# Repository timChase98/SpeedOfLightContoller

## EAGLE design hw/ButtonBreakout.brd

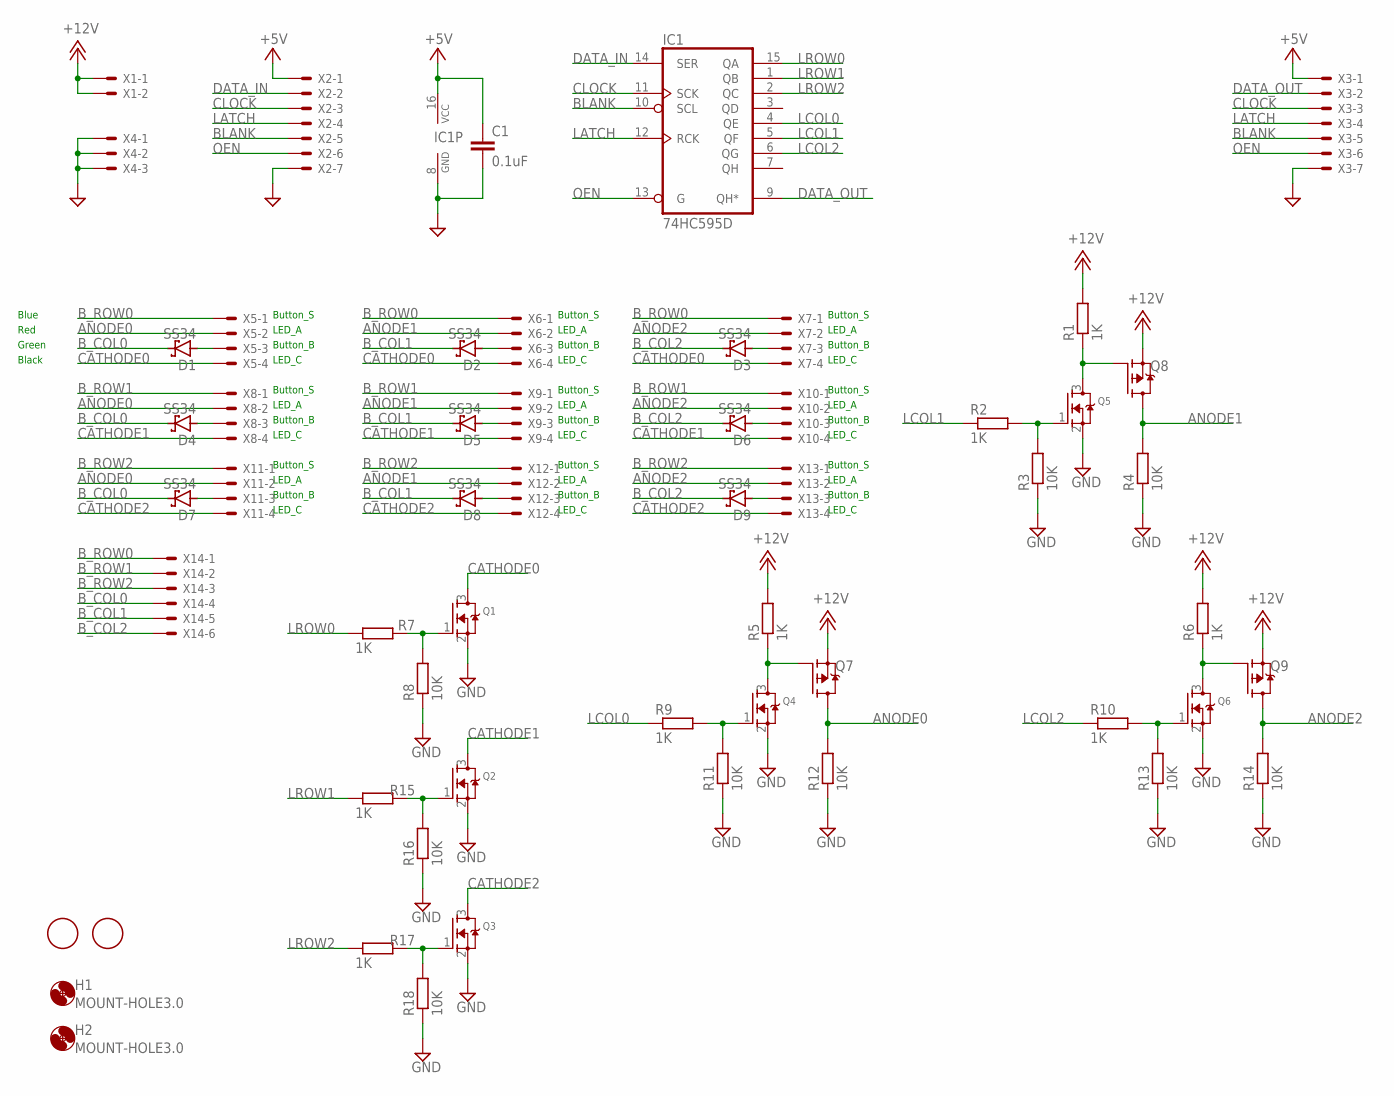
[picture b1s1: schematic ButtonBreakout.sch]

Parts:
C1: 0.1uF; C0805
D1, D2, D3, D4, D5, D6, D7, D8, D9: SS34; SMA
F1, F2: FIDUCIAL; FIDUCIAL_1MM
H1, H2: MOUNT-HOLE3.0; 3,0
IC1: 74HC595D; SO16
Q1, Q2, Q3, Q4, Q5, Q6: AO3414SOT23; SOT95P240X110-3N
Q7, Q8, Q9: AO3415; SOT95P240X110-3N
R1, R2, R5, R6, R7, R9, R10, R15, R17: 1K; R0805
R3, R4, R8, R11, R12, R13, R14, R16, R18: 10K; R0805
X1: JST-XH-02-PIN-LONG-PAD; JST-XH-02-PACKAGE-LONG-PAD
X2, X3: JST-XH-07-PIN-LONG-PAD; JST-XH-07-PACKAGE-LONG-PAD
X4: JST-XH-03-PIN-LONG-PAD; JST-XH-03-PACKAGE-LONG-PAD
X5, X6, X7, X8, X9, X10, X11, X12, X13: JST-XH-04-PIN-LONG-PAD; JST-XH-04-PACKAGE-LONG-PAD
X14: JST-XH-06-PIN-LONG-PAD; JST-XH-06-PACKAGE-LONG-PAD

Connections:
+5V: C1.1, IC1.16 (VCC), X2.1, X3.1
+12V: Q7.2 (S), Q8.2 (S), Q9.2 (S), R1.2, R5.2, R6.2, X1.1, X1.2
ANODE0: Q7.3 (D), R12.2, X5.2, X8.2, X11.2
ANODE1: Q8.3 (D), R4.2, X6.2, X9.2, X12.2
ANODE2: Q9.3 (D), R14.2, X7.2, X10.2, X13.2
BLANK: IC1.10 (SCL), X2.5, X3.5
B_COL0: D1.C, D4.C, D7.C, X14.4
B_COL1: D2.C, D5.C, D8.C, X14.5
B_COL2: D3.C, D6.C, D9.C, X14.6
B_ROW0: X5.1, X6.1, X7.1, X14.1
B_ROW1: X8.1, X9.1, X10.1, X14.2
B_ROW2: X11.1, X12.1, X13.1, X14.3
CATHODE0: Q1.3 (D), X5.4, X6.4, X7.4
CATHODE1: Q2.3 (D), X8.4, X9.4, X10.4
CATHODE2: Q3.3 (D), X11.4, X12.4, X13.4
CLOCK: IC1.11 (SCK), X2.3, X3.3
DATA_IN: IC1.14 (SER), X2.2
DATA_OUT: IC1.9 (QH*), X3.2
GND: C1.2, IC1.8 (GND), Q1.2 (S), Q2.2 (S), Q3.2 (S), Q4.2 (S), Q5.2 (S), Q6.2 (S), R3.1, R4.1, R8.1, R11.1, R12.1, R13.1, R14.1, R16.1, R18.1, X2.7, X3.7, X4.1, X4.2, X4.3
LATCH: IC1.12 (RCK), X2.4, X3.4
LCOL0: IC1.4 (QE), R9.1
LCOL1: IC1.5 (QF), R2.1
LCOL2: IC1.6 (QG), R10.1
LROW0: IC1.15 (QA), R7.1
LROW1: IC1.1 (QB), R15.1
LROW2: IC1.2 (QC), R17.1
unnamed: Q2.1 (G), R15.2, R16.2
unnamed: Q3.1 (G), R17.2, R18.2
unnamed: Q5.3 (D), Q8.1 (G), R1.1
unnamed: Q5.1 (G), R2.2, R3.2
unnamed: Q1.1 (G), R7.2, R8.2
unnamed: Q4.3 (D), Q7.1 (G), R5.1
unnamed: D1.A, X5.3
unnamed: D2.A, X6.3
unnamed: D3.A, X7.3
unnamed: D4.A, X8.3
unnamed: D5.A, X9.3
unnamed: D6.A, X10.3
unnamed: D7.A, X11.3
unnamed: D8.A, X12.3
unnamed: D9.A, X13.3
unnamed: Q4.1 (G), R9.2, R11.2
unnamed: Q6.3 (D), Q9.1 (G), R6.1
unnamed: Q6.1 (G), R10.2, R13.2
OEN: IC1.13 (G), X2.6, X3.6

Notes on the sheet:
LED_A
LED_C
Button_S
Button_B
Red
Black
Blue
Green

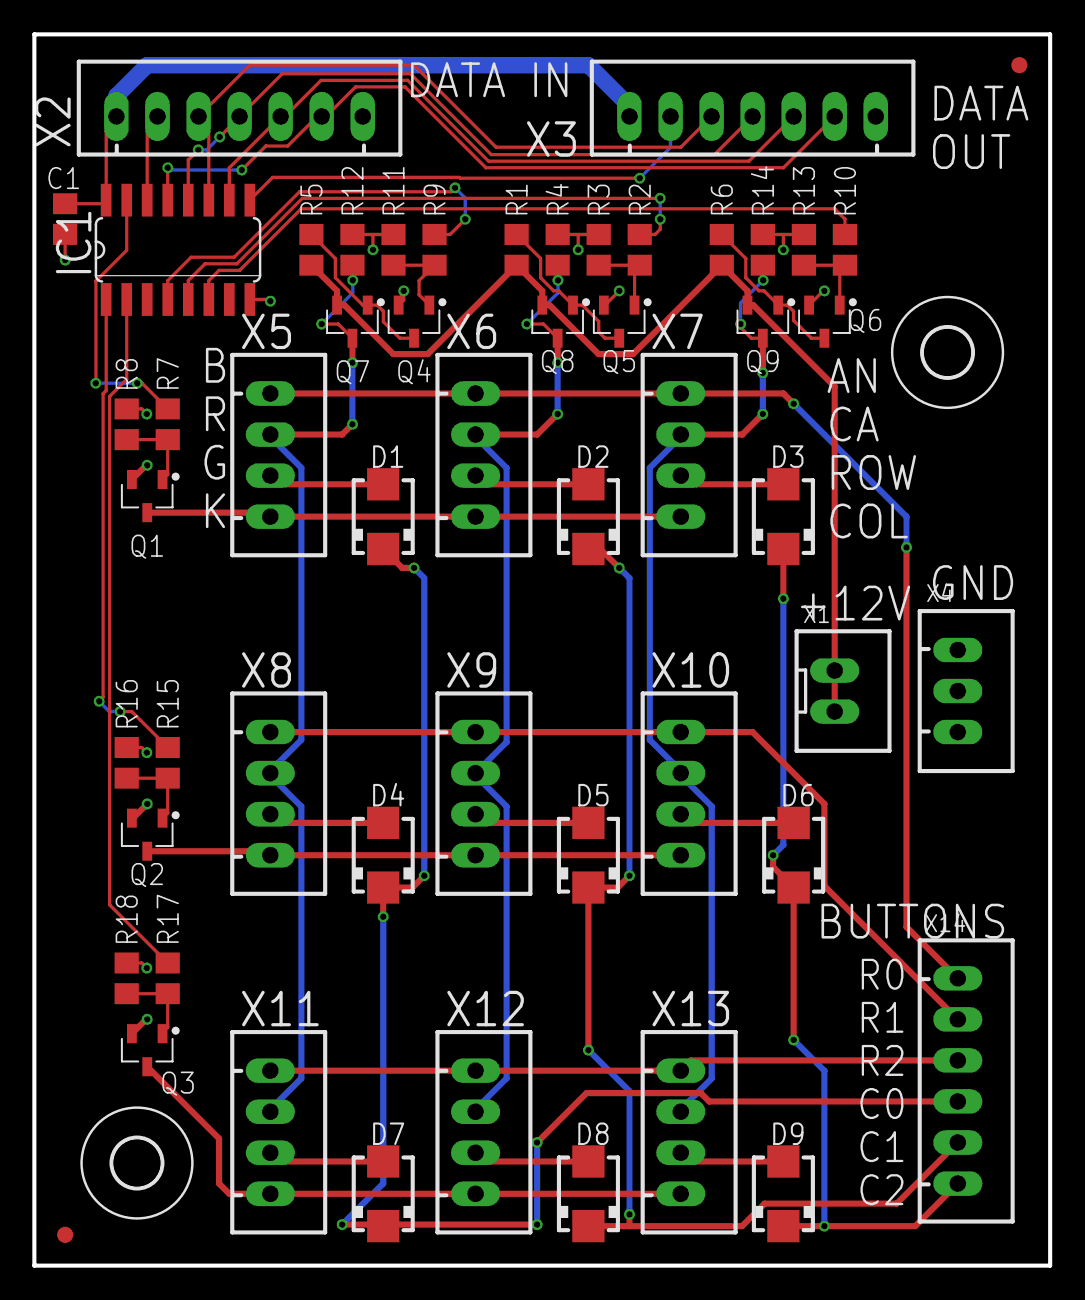
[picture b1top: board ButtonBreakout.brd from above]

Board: 2 copper layers, 62.9 x 76.2 mm, 56 parts (0 on the bottom side), 45 nets.

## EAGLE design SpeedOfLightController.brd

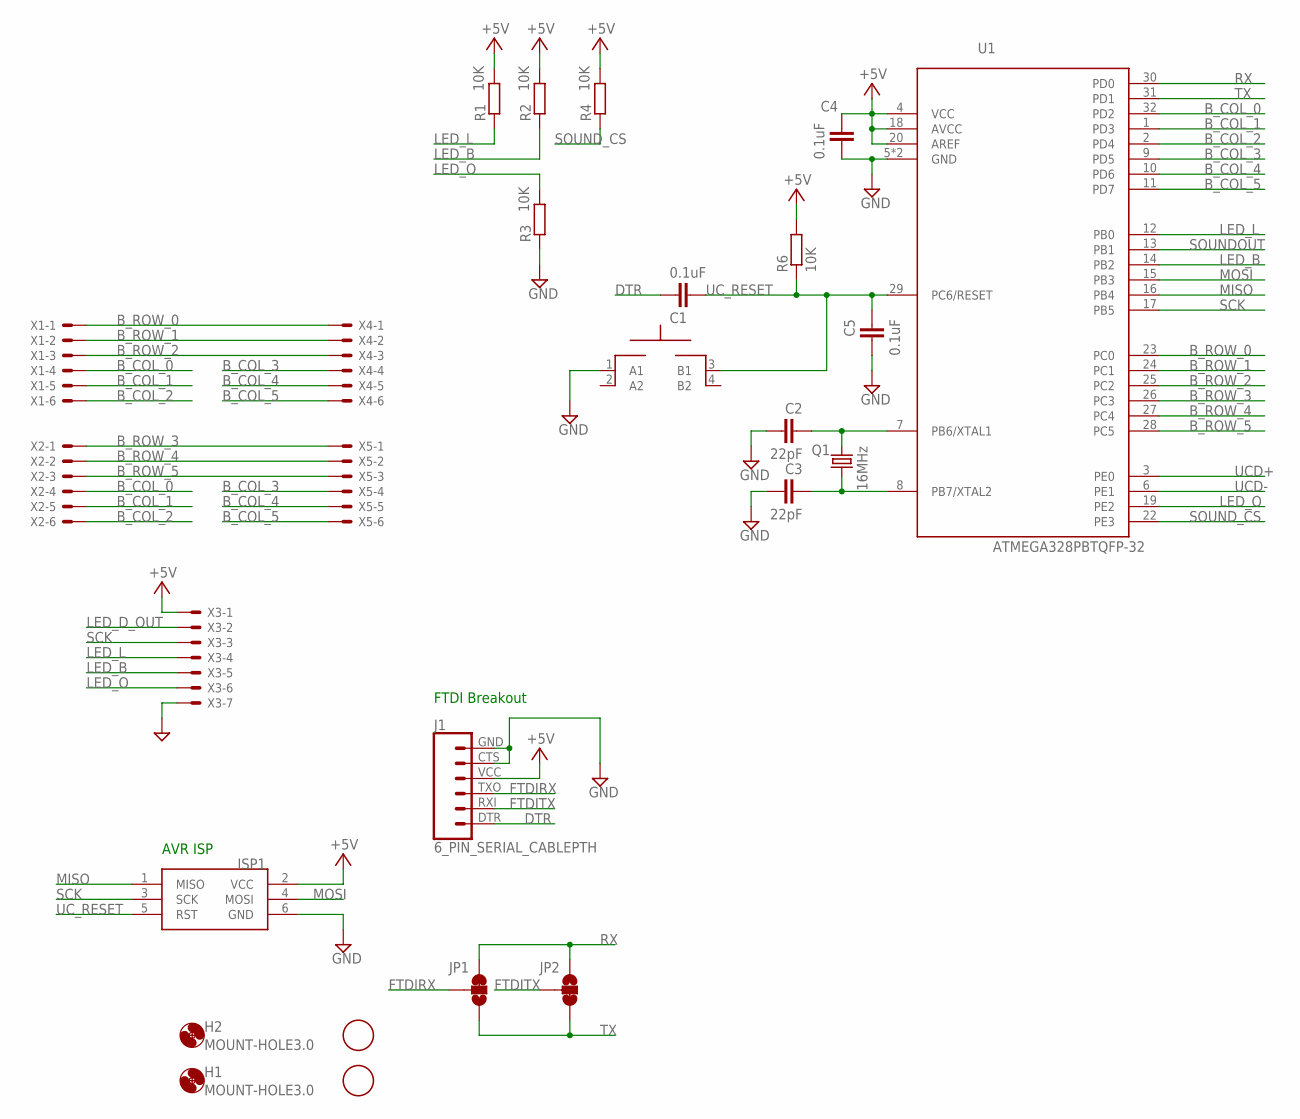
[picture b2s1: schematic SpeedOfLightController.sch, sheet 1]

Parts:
C1, C4, C5: 0.1uF; C0805
C2, C3: 22pF; C0805
F1, F2: FIDUCIAL; FIDUCIAL_1MM
H1, H2: MOUNT-HOLE3.0; 3,0
ISP1: AVRISP-6; AVRISP
J1: 6_PIN_SERIAL_CABLEPTH; FTDI_BASIC
JP1, JP2: JUMPER-SMT_3_1-NC_TRACE_SILK; SMT-JUMPER_3_1-NC_TRACE_SILK
Q1: 16MHz; HC49UP
R1, R2, R3, R4, R6: 10K; R0805
SW1: MOMENTARYBUTTON; SPST_NO_SMD
U1: ATMEGA328PBTQFP-32; QFP80P900X900X120-32N
X1, X2, X4, X5: JST-XH-06-PIN-LONG-PAD; JST-XH-06-PACKAGE-LONG-PAD
X3: JST-XH-07-PIN-LONG-PAD; JST-XH-07-PACKAGE-LONG-PAD

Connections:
+5V: C4.2, ISP1.2 (VCC), J1.VCC (4), R1.2, R2.2, R4.2, R6.2, U1.4 (VCC), U1.18 (AVCC), U1.20 (AREF), X3.1; also elsewhere on the board
B_COL_0: U1.32 (PD2), X1.4, X2.4
B_COL_1: U1.1 (PD3), X1.5, X2.5
B_COL_2: U1.2 (PD4), X1.6, X2.6
B_COL_3: U1.9 (PD5), X4.4, X5.4
B_COL_4: U1.10 (PD6), X4.5, X5.5
B_COL_5: U1.11 (PD7), X4.6, X5.6
B_ROW_0: U1.23 (PC0), X1.1, X4.1
B_ROW_1: U1.24 (PC1), X1.2, X4.2
B_ROW_2: U1.25 (PC2), X1.3, X4.3
B_ROW_3: U1.26 (PC3), X2.1, X5.1
B_ROW_4: U1.27 (PC4), X2.2, X5.2
B_ROW_5: U1.28 (PC5), X2.3, X5.3
DTR: C1.2, J1.DTR (1)
FTDIRX: J1.TXO (3), JP1.2
FTDITX: J1.RXI (2), JP2.2
GND: C2.1, C3.1, C4.1, C5.1, ISP1.6 (GND), J1.CTS (5), J1.GND (6), R3.1, SW1.1 (A1), U1.5 (GND), U1.21 (GND), X3.7; also elsewhere on the board
LED_B: R2.1, U1.14 (PB2), X3.5; also elsewhere on the board
LED_D_OUT: X3.2; also elsewhere on the board
LED_L: R1.1, U1.12 (PB0), X3.4; also elsewhere on the board
LED_O: R3.2, U1.19 (PE2), X3.6; also elsewhere on the board
MISO: ISP1.1 (MISO), U1.16 (PB4); also elsewhere on the board
MOSI: ISP1.4 (MOSI), U1.15 (PB3); also elsewhere on the board
unnamed: C2.2, Q1.1, U1.7 (PB6/XTAL1)
unnamed: C3.2, Q1.2, U1.8 (PB7/XTAL2)
RX: JP1.3, JP2.1, U1.30 (PD0)
SCK: ISP1.3 (SCK), U1.17 (PB5), X3.3; also elsewhere on the board
SOUNDOUT: U1.13 (PB1); also elsewhere on the board
SOUND_CS: R4.1, U1.22 (PE3); also elsewhere on the board
TX: JP1.1, JP2.3, U1.31 (PD1)
UCD+: U1.3 (PE0); also elsewhere on the board
UCD-: U1.6 (PE1); also elsewhere on the board
UC_RESET: C1.1, C5.2, ISP1.5 (RST), R6.1, SW1.3 (B1), U1.29 (PC6/RESET)

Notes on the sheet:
AVR ISP
FTDI Breakout

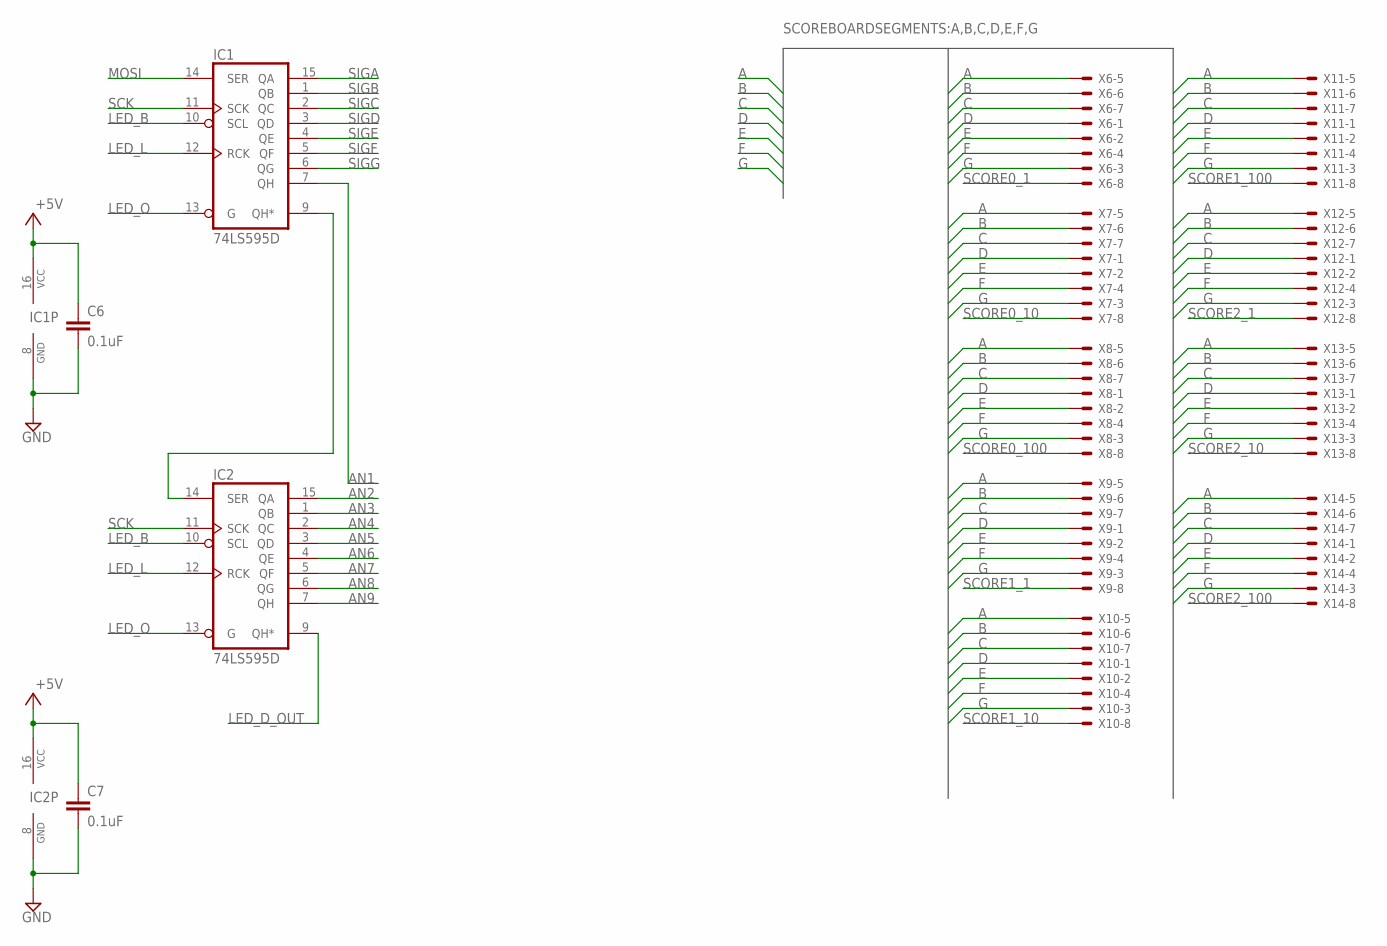
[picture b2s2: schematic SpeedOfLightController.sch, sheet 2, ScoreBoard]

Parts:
C6, C7: 0.1uF; C0805
IC1, IC2: 74LS595D; SO16
X6, X7, X8, X9, X10, X11, X12, X13, X14: JST-XH-08-PIN-LONG-PAD; JST-XH-08-PACKAGE-LONG-PAD

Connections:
+5V: C6.1, C7.1, IC1.16 (VCC), IC2.16 (VCC); also elsewhere on the board
A: X6.5, X7.5, X8.5, X9.5, X10.5, X11.5, X12.5, X13.5, X14.5; also elsewhere on the board
AN1: IC1.7 (QH); also elsewhere on the board
AN2: IC2.15 (QA); also elsewhere on the board
AN3: IC2.1 (QB); also elsewhere on the board
AN4: IC2.2 (QC); also elsewhere on the board
AN5: IC2.3 (QD); also elsewhere on the board
AN6: IC2.4 (QE); also elsewhere on the board
AN7: IC2.5 (QF); also elsewhere on the board
AN8: IC2.6 (QG); also elsewhere on the board
AN9: IC2.7 (QH); also elsewhere on the board
B: X6.6, X7.6, X8.6, X9.6, X10.6, X11.6, X12.6, X13.6, X14.6; also elsewhere on the board
C: X6.7, X7.7, X8.7, X9.7, X10.7, X11.7, X12.7, X13.7, X14.7; also elsewhere on the board
D: X6.1, X7.1, X8.1, X9.1, X10.1, X11.1, X12.1, X13.1, X14.1; also elsewhere on the board
E: X6.2, X7.2, X8.2, X9.2, X10.2, X11.2, X12.2, X13.2, X14.2; also elsewhere on the board
F: X6.4, X7.4, X8.4, X9.4, X10.4, X11.4, X12.4, X13.4, X14.4; also elsewhere on the board
G: X6.3, X7.3, X8.3, X9.3, X10.3, X11.3, X12.3, X13.3, X14.3; also elsewhere on the board
GND: C6.2, C7.2, IC1.8 (GND), IC2.8 (GND); also elsewhere on the board
LED_B: IC1.10 (SCL), IC2.10 (SCL); also elsewhere on the board
LED_D_OUT: IC2.9 (QH*); also elsewhere on the board
LED_L: IC1.12 (RCK), IC2.12 (RCK); also elsewhere on the board
LED_O: IC1.13 (G), IC2.13 (G); also elsewhere on the board
MOSI: IC1.14 (SER); also elsewhere on the board
unnamed: IC1.9 (QH*), IC2.14 (SER)
SCK: IC1.11 (SCK), IC2.11 (SCK); also elsewhere on the board
SCORE0_1: X6.8; also elsewhere on the board
SCORE0_10: X7.8; also elsewhere on the board
SCORE0_100: X8.8; also elsewhere on the board
SCORE1_1: X9.8; also elsewhere on the board
SCORE1_10: X10.8; also elsewhere on the board
SCORE1_100: X11.8; also elsewhere on the board
SCORE2_1: X12.8; also elsewhere on the board
SCORE2_10: X13.8; also elsewhere on the board
SCORE2_100: X14.8; also elsewhere on the board
SIGA: IC1.15 (QA); also elsewhere on the board
SIGB: IC1.1 (QB); also elsewhere on the board
SIGC: IC1.2 (QC); also elsewhere on the board
SIGD: IC1.3 (QD); also elsewhere on the board
SIGE: IC1.4 (QE); also elsewhere on the board
SIGF: IC1.5 (QF); also elsewhere on the board
SIGG: IC1.6 (QG); also elsewhere on the board

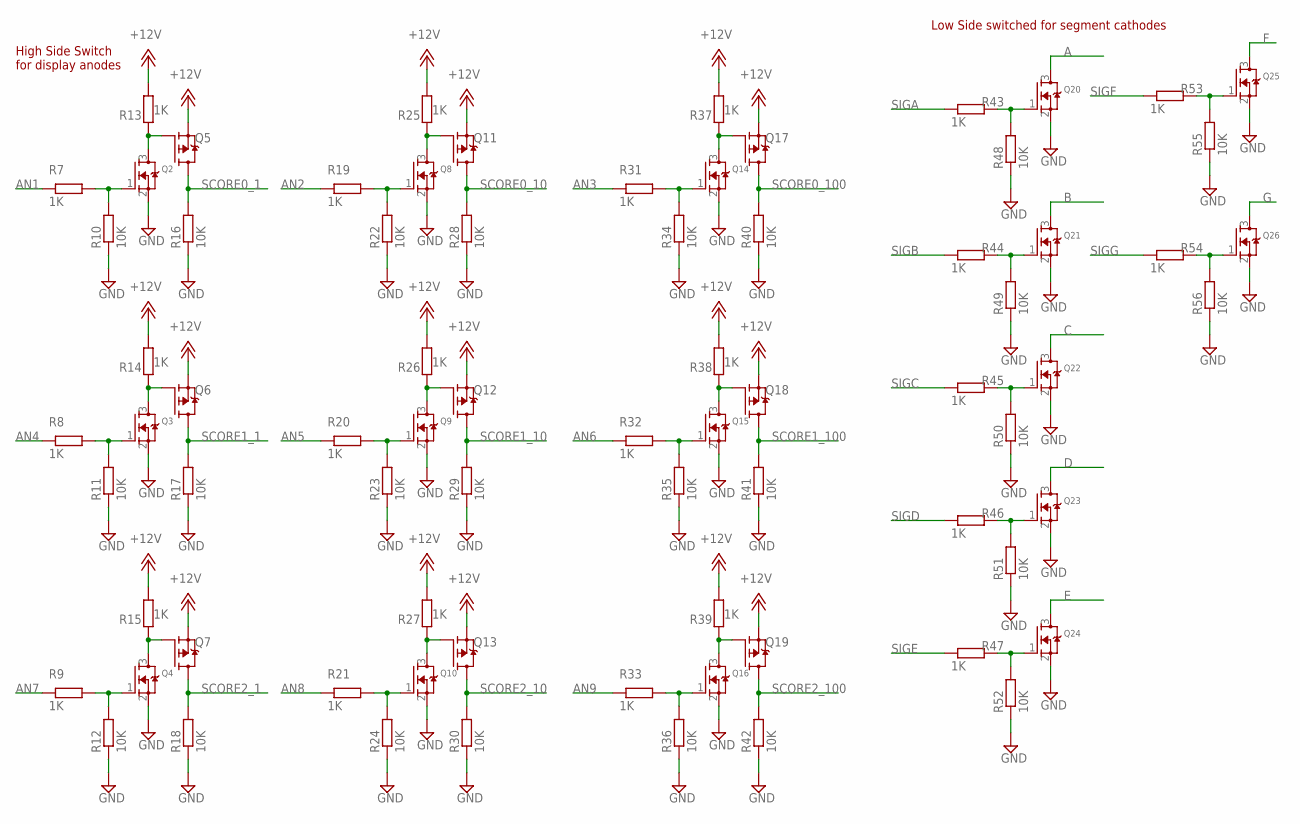
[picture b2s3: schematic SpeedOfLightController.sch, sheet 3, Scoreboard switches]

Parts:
Q2, Q3, Q4, Q8, Q9, Q10, Q14, Q15, Q16, Q20, Q21, Q22, Q23, Q24, Q25, Q26: AO3414SOT23; SOT95P240X110-3N
Q5, Q6, Q7, Q11, Q12, Q13, Q17, Q18, Q19: AO3415; SOT95P240X110-3N
R7, R8, R9, R13, R14, R15, R19, R20, R21, R25, R26, R27, R31, R32, R33, R37, R38, R39, R43, R44, R45, R46, R47, R53, R54: 1K; R0805
R10, R11, R12, R16, R17, R18, R22, R23, R24, R28, R29, R30, R34, R35, R36, R40, R41, R42, R48, R49, R50, R51, R52, R55, R56: 10K; R0805

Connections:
+12V: Q5.2 (S), Q6.2 (S), Q7.2 (S), Q11.2 (S), Q12.2 (S), Q13.2 (S), Q17.2 (S), Q18.2 (S), Q19.2 (S), R13.2, R14.2, R15.2, R25.2, R26.2, R27.2, R37.2, R38.2, R39.2; also elsewhere on the board
A: Q20.3 (D); also elsewhere on the board
AN1: R7.1; also elsewhere on the board
AN2: R19.1; also elsewhere on the board
AN3: R31.1; also elsewhere on the board
AN4: R8.1; also elsewhere on the board
AN5: R20.1; also elsewhere on the board
AN6: R32.1; also elsewhere on the board
AN7: R9.1; also elsewhere on the board
AN8: R21.1; also elsewhere on the board
AN9: R33.1; also elsewhere on the board
B: Q21.3 (D); also elsewhere on the board
C: Q22.3 (D); also elsewhere on the board
D: Q23.3 (D); also elsewhere on the board
E: Q24.3 (D); also elsewhere on the board
F: Q25.3 (D); also elsewhere on the board
G: Q26.3 (D); also elsewhere on the board
GND: Q2.2 (S), Q3.2 (S), Q4.2 (S), Q8.2 (S), Q9.2 (S), Q10.2 (S), Q14.2 (S), Q15.2 (S), Q16.2 (S), Q20.2 (S), Q21.2 (S), Q22.2 (S), Q23.2 (S), Q24.2 (S), Q25.2 (S), Q26.2 (S), R10.1, R11.1, R12.1, R16.1, R17.1, R18.1, R22.1, R23.1, R24.1, R28.1, R29.1, R30.1, R34.1, R35.1, R36.1, R40.1, R41.1, R42.1, R48.1, R49.1, R50.1, R51.1, R52.1, R55.1, R56.1; also elsewhere on the board
unnamed: Q21.1 (G), R44.2, R49.2
unnamed: Q22.1 (G), R45.2, R50.2
unnamed: Q23.1 (G), R46.2, R51.2
unnamed: Q24.1 (G), R47.2, R52.2
unnamed: Q20.1 (G), R43.2, R48.2
unnamed: Q25.1 (G), R53.2, R55.2
unnamed: Q26.1 (G), R54.2, R56.2
unnamed: Q2.1 (G), R7.2, R10.2
unnamed: Q8.1 (G), R19.2, R22.2
unnamed: Q14.1 (G), R31.2, R34.2
unnamed: Q3.1 (G), R8.2, R11.2
unnamed: Q9.1 (G), R20.2, R23.2
unnamed: Q15.1 (G), R32.2, R35.2
unnamed: Q4.1 (G), R9.2, R12.2
unnamed: Q10.1 (G), R21.2, R24.2
unnamed: Q16.1 (G), R33.2, R36.2
unnamed: Q16.3 (D), Q19.1 (G), R39.1
unnamed: Q10.3 (D), Q13.1 (G), R27.1
unnamed: Q4.3 (D), Q7.1 (G), R15.1
unnamed: Q3.3 (D), Q6.1 (G), R14.1
unnamed: Q9.3 (D), Q12.1 (G), R26.1
unnamed: Q15.3 (D), Q18.1 (G), R38.1
unnamed: Q14.3 (D), Q17.1 (G), R37.1
unnamed: Q8.3 (D), Q11.1 (G), R25.1
unnamed: Q2.3 (D), Q5.1 (G), R13.1
SCORE0_1: Q5.3 (D), R16.2; also elsewhere on the board
SCORE0_10: Q11.3 (D), R28.2; also elsewhere on the board
SCORE0_100: Q17.3 (D), R40.2; also elsewhere on the board
SCORE1_1: Q6.3 (D), R17.2; also elsewhere on the board
SCORE1_10: Q12.3 (D), R29.2; also elsewhere on the board
SCORE1_100: Q18.3 (D), R41.2; also elsewhere on the board
SCORE2_1: Q7.3 (D), R18.2; also elsewhere on the board
SCORE2_10: Q13.3 (D), R30.2; also elsewhere on the board
SCORE2_100: Q19.3 (D), R42.2; also elsewhere on the board
SIGA: R43.1; also elsewhere on the board
SIGB: R44.1; also elsewhere on the board
SIGC: R45.1; also elsewhere on the board
SIGD: R46.1; also elsewhere on the board
SIGE: R47.1; also elsewhere on the board
SIGF: R53.1; also elsewhere on the board
SIGG: R54.1; also elsewhere on the board

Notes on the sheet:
High Side Switch for display anodes
Low Side switched for segment cathodes

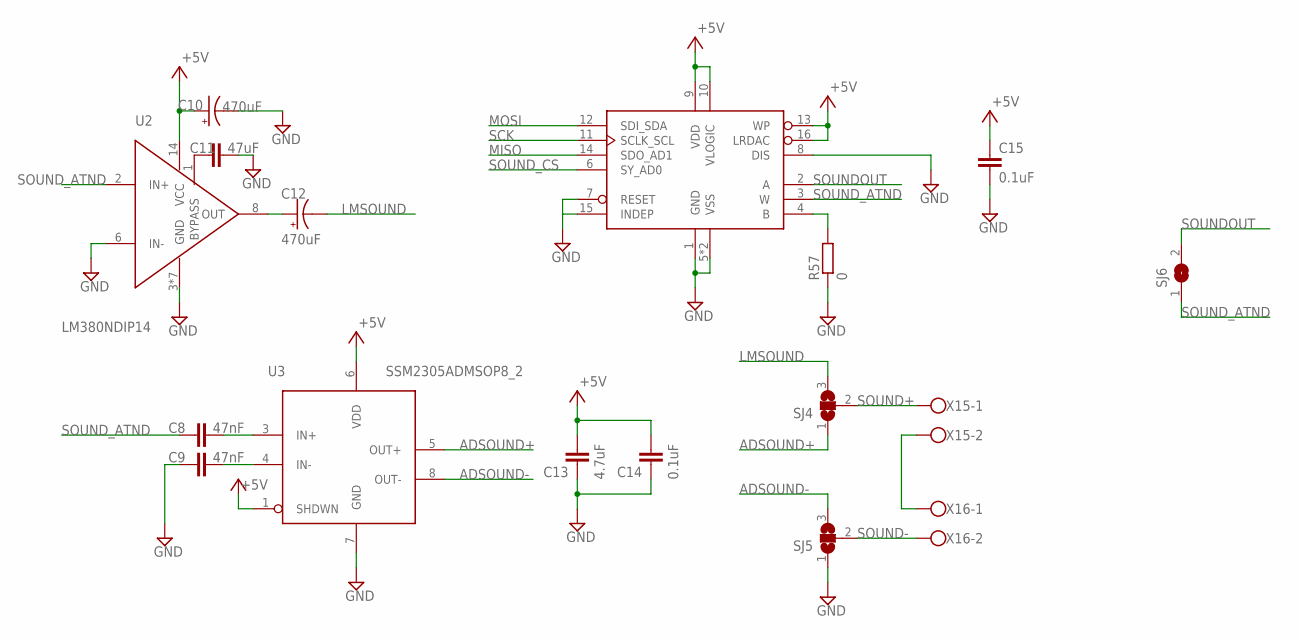
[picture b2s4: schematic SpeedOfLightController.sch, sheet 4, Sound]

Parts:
C8, C9: 47nF; C0805
C10, C12: 470uF; 140CLH-0810
C11: 47uF; C0805
C13: 4.7uF; C0805
C14, C15: 0.1uF; C0805
R57: 0; R0805W
SJ4, SJ5: SJ2WW; SJ_2W
SJ6: SJ
U2: LM380NDIP14; DIP762W53P254L1969H508Q14B
U3: SSM2305ADMSOP8_2; SOP65P490X95-8N
U4: AD5141ADLFCSP3; QFN50P300X300X80-17T160N
X15, X16: 1X02_5MM_SCREW; W237-102

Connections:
+5V: C10.+, C13.2, C14.2, C15.1, U2.14 (VCC), U3.1 (SHDWN), U3.6 (VDD), U4.9 (VDD), U4.10 (VLOGIC), U4.13 (WP), U4.16 (LRDAC); also elsewhere on the board
ADSOUND+: SJ4.1, U3.5 (OUT+)
ADSOUND-: SJ5.3, U3.8 (OUT-)
GND: C9.1, C10.-, C11.2, C13.1, C14.1, C15.2, R57.1, SJ5.1, U2.3 (GND), U2.4 (GND), U2.5 (GND), U2.6 (IN-), U2.7 (GND), U2.10 (GND), U2.11 (GND), U2.12 (GND), U3.7 (GND), U4.1 (GND), U4.5 (VSS), U4.7 (RESET), U4.8 (DIS), U4.15 (INDEP), U4.17 (VSS); also elsewhere on the board
LMSOUND: C12.-, SJ4.3
MISO: U4.14 (SDO_AD1); also elsewhere on the board
MOSI: U4.12 (SDI_SDA); also elsewhere on the board
unnamed: X15.2, X16.1
unnamed: C12.+, U2.8 (OUT)
unnamed: C11.1, U2.1 (BYPASS)
unnamed: C9.2, U3.4 (IN-)
unnamed: C8.2, U3.3 (IN+)
unnamed: R57.2, U4.4 (B)
SCK: U4.11 (SCLK_SCL); also elsewhere on the board
SOUND+: SJ4.2, X15.1
SOUND-: SJ5.2, X16.2
SOUNDOUT: SJ6.2, U4.2 (A); also elsewhere on the board
SOUND_ATND: C8.1, SJ6.1, U2.2 (IN+), U4.3 (W)
SOUND_CS: U4.6 (SY_AD0); also elsewhere on the board

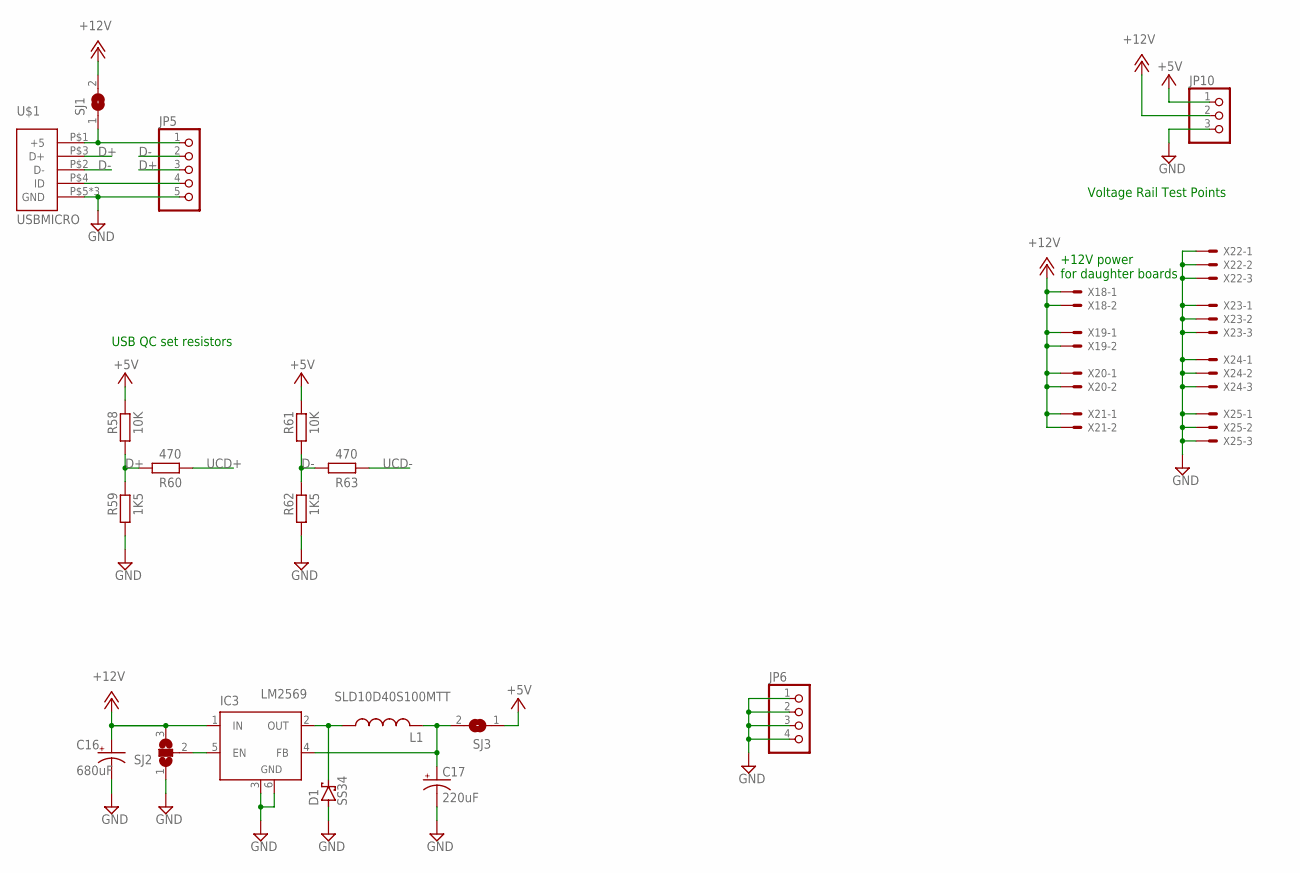
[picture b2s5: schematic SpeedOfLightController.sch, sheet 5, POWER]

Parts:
C16: 680uF; 140CLH-0810
C17: 220uF; 140CLH-0810
D1: SS34; SMA
IC3: LM2596S; TO263-5
JP5: PINHD-1X5; 1X05
JP6: PINHD-1X4; 1X04
JP10: PINHD-1X3; 1X03
L1: SLD10D40S100MTT; SMD10.5X10.3
R58, R61: 10K; R0805
R59, R62: 1K5; R0805
R60, R63: 470; R0805
SJ1, SJ3: SJ
SJ2: SJ2WW; SJ_2W
U$1: USBMICRO
X18, X19, X20, X21: JST-XH-02-PIN-LONG-PAD; JST-XH-02-PACKAGE-LONG-PAD
X22, X23, X24, X25: JST-XH-03-PIN-LONG-PAD; JST-XH-03-PACKAGE-LONG-PAD

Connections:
+5V: JP10.1, R58.2, R61.1, SJ3.1; also elsewhere on the board
+12V: C16.+, IC3.1 (IN), JP10.2, SJ1.2, SJ2.3, X18.1, X18.2, X19.1, X19.2, X20.1, X20.2, X21.1, X21.2; also elsewhere on the board
D+: JP5.3, R58.1, R59.2, R60.2, U$1.P$3 (D+)
D-: JP5.2, R61.2, R62.1, R63.1, U$1.P$2 (D-)
GND: C16.-, C17.-, D1.A, IC3.3 (GND), IC3.6 (GND), JP5.5, JP6.1, JP6.2, JP6.3, JP6.4, JP10.3, R59.1, R62.2, SJ2.1, U$1.P$5 (GND), U$1.P$6 (GND), U$1.P$8 (GND), X22.1, X22.2, X22.3, X23.1, X23.2, X23.3, X24.1, X24.2, X24.3, X25.1, X25.2, X25.3; also elsewhere on the board
unnamed: JP5.1, SJ1.1, U$1.P$1 (+5)
unnamed: JP5.4, U$1.P$4 (ID)
unnamed: D1.C, IC3.2 (OUT), L1.P$1 (1)
unnamed: IC3.5 (EN), SJ2.2
unnamed: C17.+, IC3.4 (FB), L1.P$2 (2), SJ3.2
UCD+: R60.1; also elsewhere on the board
UCD-: R63.2; also elsewhere on the board

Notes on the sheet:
Voltage Rail Test Points
+12V power for daughter boards
USB QC set resistors
LM2569

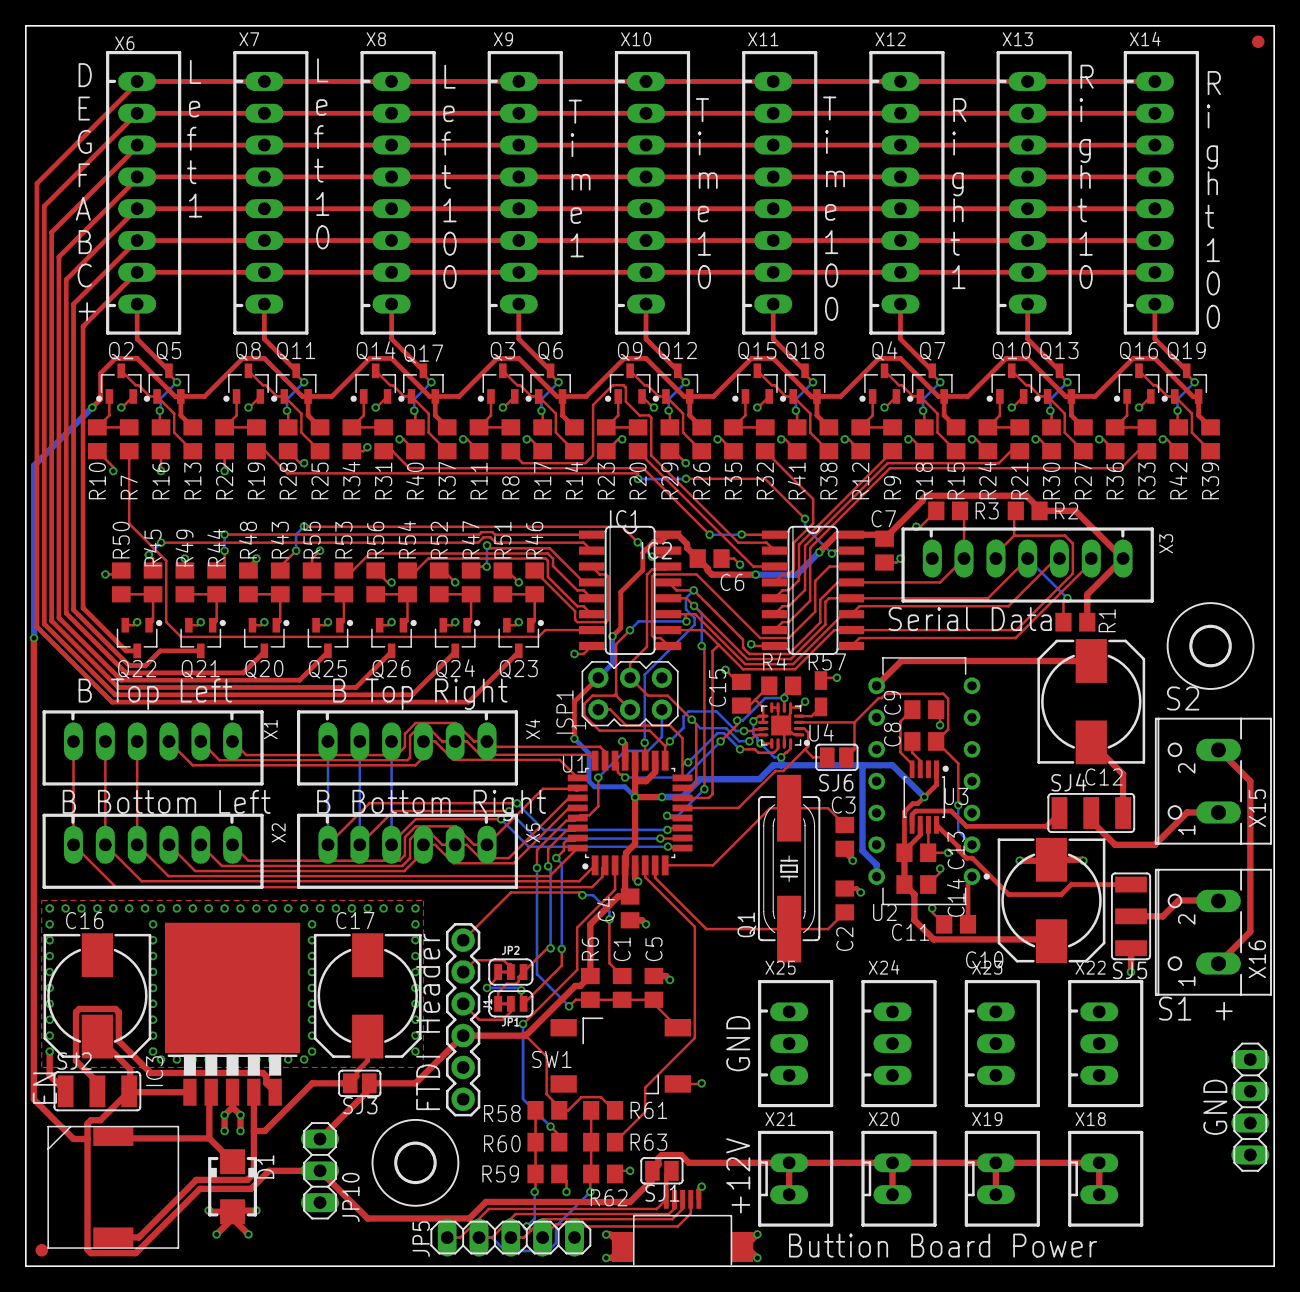
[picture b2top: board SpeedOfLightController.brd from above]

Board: 2 copper layers, 99.7 x 99.1 mm, 157 parts (0 on the bottom side), 111 nets.

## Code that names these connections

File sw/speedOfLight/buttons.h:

/*
* buttons.h
*
* Created: 11/27/2019 9:33:37 AM
*  Author: tchase
*/


#ifndef BUTTONS_H_
#define BUTTONS_H_

#define  LED_L 0 // led latch on B.0
#define  LED_B 3 // led blank on E.3

enum ScoreDisplay {
	LEFT = 0,
	TIMER = 1,
	RIGHT = 2,
	LEFT1 = 0,
	LEFT10 = 1,
	LEFT100 = 2,
	TIMER1 = 3,
	TIMER10 = 4,
	TIMER100 = 5,
	RIGHT1 = 6,
	RIGHT10 = 7,
	RIGHT100 = 8,
	
};


void buttonsInit();
void clearLeds(uint8_t);

void spiSetup();
void tmrSetup();
uint8_t isButtonDown(uint8_t x, uint8_t y);
void setButtonLed(uint8_t x, uint8_t y, uint8_t value);
int getButtonLed(uint8_t x, uint8_t y);
void setScore(uint8_t display, uint16_t value);
void setScoreSegment(uint8_t segment, uint8_t val);


const extern uint8_t sevenSegmentDecode[];


#endif /* BUTTONS_H_ */

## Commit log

2019-11-05 inital
2019-11-11 USBPD design review
2019-11-12 Change to 100mm square board
2019-11-13 Board Redone with notes from Ben
2019-11-13 Updated rendered schematics
2019-11-13 Render all pages...
2019-11-25 commit before messing with the git settings
2019-11-25 Moving Stuff
2019-11-25 Done Moving Stuff?
2019-11-25 Moved Stuff?
2019-11-25 added software to git
2019-11-25 added atmel studio files
2019-11-27 Moved hardware into HW folder
2019-11-27 added software prodject
2019-11-27 reorginized button and LED code
2019-12-05 initial real game
2019-12-05 added some score display & surprisingly compiles
2019-12-07 added test code
2019-12-07 mv to jesh
2019-12-09 edited mux controller
2019-12-10 mv to jsh
2019-12-10 Fixed stuff
2019-12-10 pushed modify button code
2019-12-10 move to jsh
2019-12-11 fixed buttons and leds
2019-12-11 works i guess
2019-12-11 2tim
2019-12-12 todo fix multiplier
2019-12-12 use this commit if everything breaks
2019-12-14 final before presentation
2019-12-22 fixed DC converter part number
2019-12-22 Fixed PDF generation

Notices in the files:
parts and their libraries:
SparkFun-Jumpers: Licensing: Creative Commons ShareAlike 4.0 International - https://creativecommons.org/licenses/by-sa/4.0
